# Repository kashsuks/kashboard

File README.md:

# kashboard

**kasboard** is a devboard that is (sorta) based off me. It is a rp2040 based devboard that follows [this](https://blueprint.hackclub.com/guides/devboard). I added a neopixel _APA102_ that will act as a status light to indicate when the board is turned on and when it is not.

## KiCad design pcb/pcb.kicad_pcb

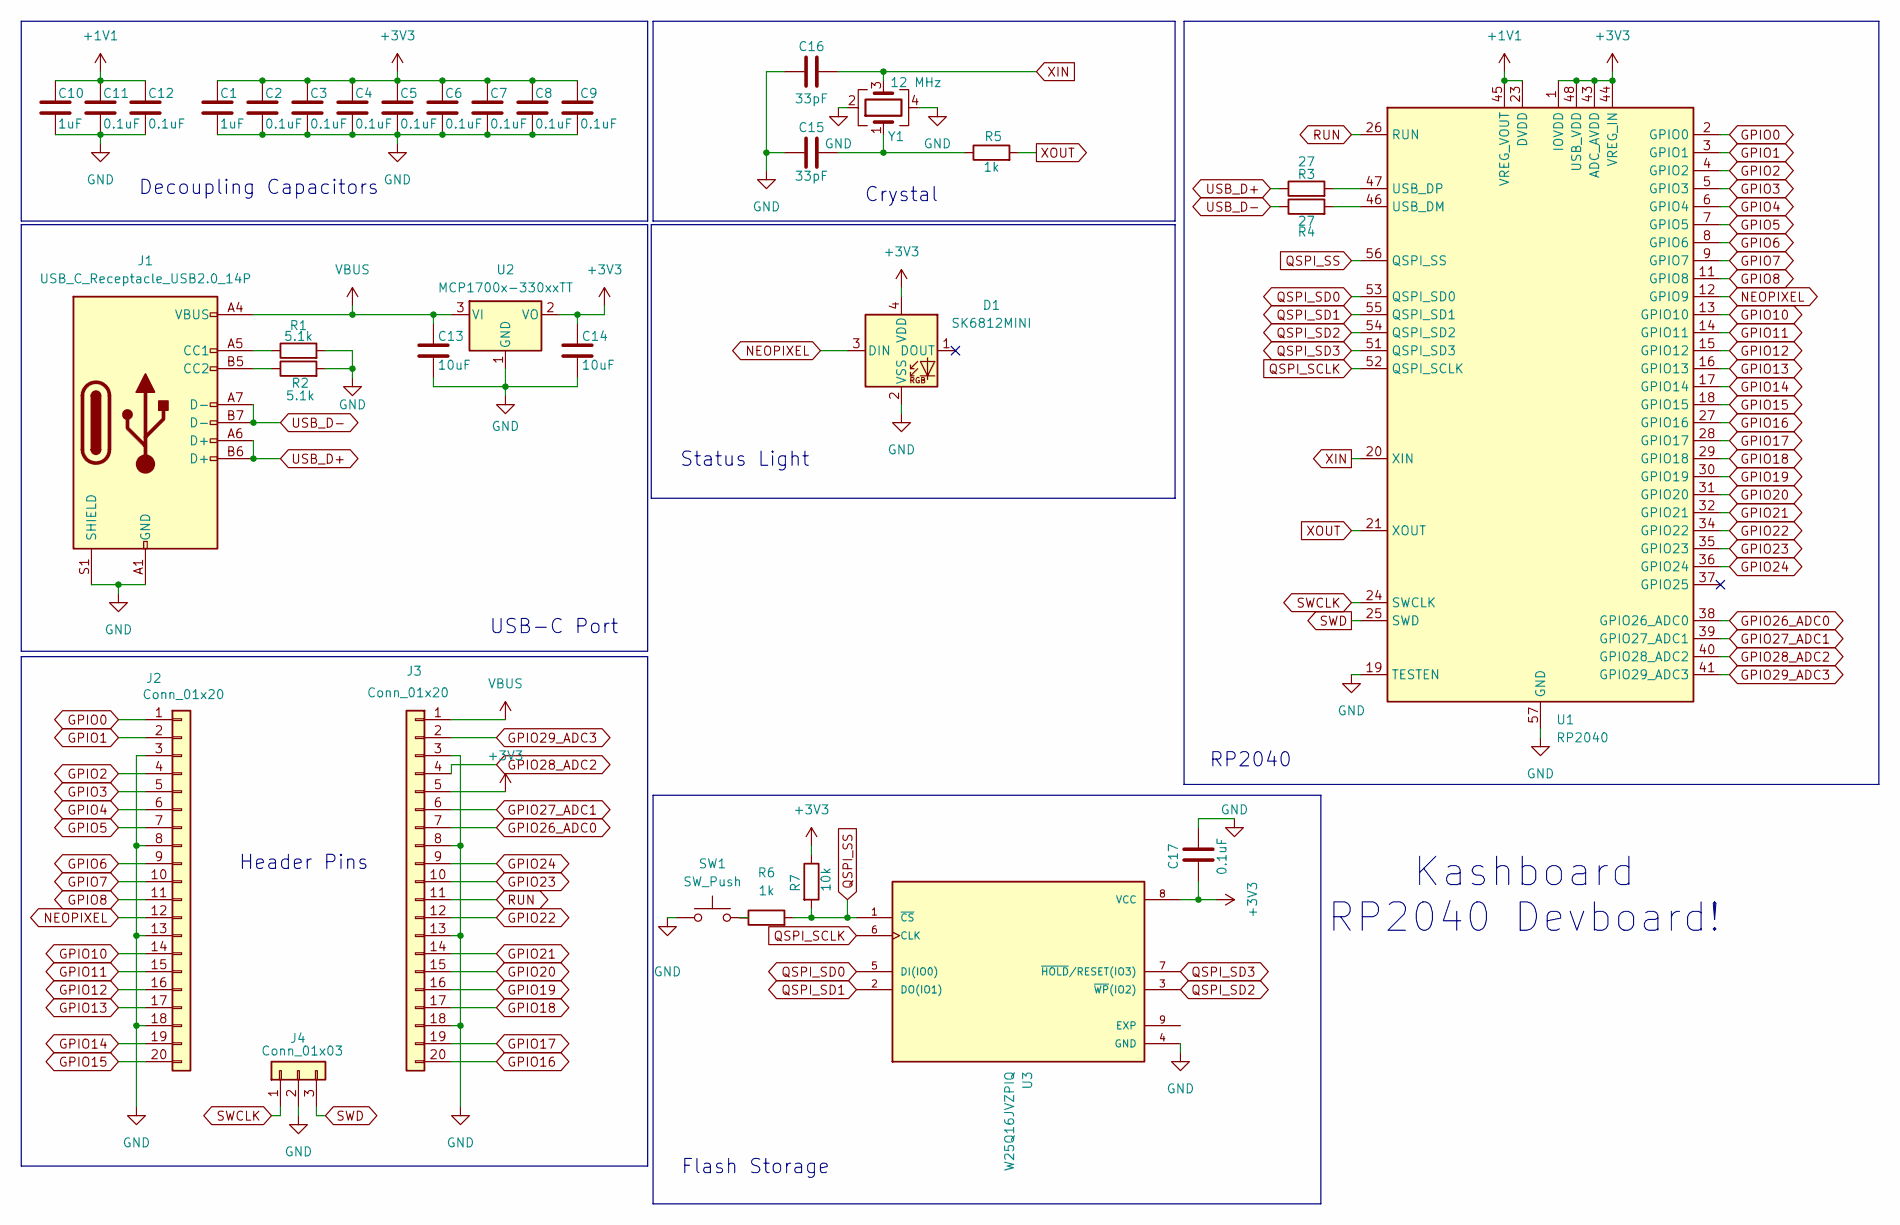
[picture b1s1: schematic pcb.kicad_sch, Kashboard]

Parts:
C1, C10: 1uF; C_0402_1005Metric
C2, C3, C4, C5, C6, C7, C8, C9, C11, C12, C17: 0.1uF; C_0402_1005Metric
C13, C14: 10uF; C_0402_1005Metric
C15, C16: 33pF; C_0402_1005Metric
D1: SK6812MINI; LED_SK6812MINI_PLCC4_3.5x3.5mm_P1.75mm
J1: USB_C_Receptacle_USB2.0_14P; USB_C_Receptacle_HRO_TYPE-C-31-M-12
J2, J3: Conn_01x20; PinHeader_1x20_P2.54mm_Vertical
J4: Conn_01x03; PinHeader_1x03_P2.54mm_Vertical
R1, R2: 5.1k; R_0402_1005Metric
R3, R4: 27; R_0402_1005Metric
R5, R6: 1k; R_0402_1005Metric
R7: 10k; R_0402_1005Metric
SW1: SW_Push; SW_Push_SPST_NO_Alps_SKRK
U1: RP2040; QFN-56-1EP_7x7mm_P0.4mm_EP3.2x3.2mm
U2: MCP1700x-330xxTT; SOT-23
U3: W25Q16JVZPIQ; Winbond_USON-8-1EP_3x2mm_P0.5mm_EP0.2x1.6mm
Y1: 12 MHz; Crystal_SMD_3225-4Pin_3.2x2.5mm

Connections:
+1V1: C10.1, C11.1, C12.1, U1.23 (DVDD), U1.45 (VREG_VOUT), U1.50 (DVDD)
+3V3: C1.1, C2.1, C3.1, C4.1, C5.1, C6.1, C7.1, C8.1, C9.1, C14.2, C17.2, D1.4 (VDD), J3.5, R7.1, U1.1 (IOVDD), U1.10 (IOVDD), U1.22 (IOVDD), U1.33 (IOVDD), U1.42 (IOVDD), U1.43 (ADC_AVDD), U1.44 (VREG_IN), U1.48 (USB_VDD), U1.49 (IOVDD), U2.2 (VO), U3.8 (VCC); also elsewhere on the board
GND: C1.2, C2.2, C3.2, C4.2, C5.2, C6.2, C7.2, C8.2, C9.2, C10.2, C11.2, C12.2, C13.1, C14.1, C15.1, C16.1, C17.1, D1.2 (VSS), J1.A1 (GND), J1.A12 (GND), J1.B1 (GND), J1.B12 (GND), J1.S1 (SHIELD), J2.3, J2.8, J2.13, J2.18, J3.3, J3.8, J3.13, J3.18, J4.2, R1.2, R2.2, SW1.1, U1.19 (TESTEN), U1.57 (GND), U2.1 (GND), U3.4 (GND), Y1.2, Y1.4; also elsewhere on the board
GPIO0: J2.1, U1.2 (GPIO0)
GPIO1: J2.2, U1.3 (GPIO1)
GPIO2: J2.4, U1.4 (GPIO2)
GPIO3: J2.5, U1.5 (GPIO3)
GPIO4: J2.6, U1.6 (GPIO4)
GPIO5: J2.7, U1.7 (GPIO5)
GPIO6: J2.9, U1.8 (GPIO6)
GPIO7: J2.10, U1.9 (GPIO7)
GPIO8: J2.11, U1.11 (GPIO8)
GPIO10: J2.14, U1.13 (GPIO10)
GPIO11: J2.15, U1.14 (GPIO11)
GPIO12: J2.16, U1.15 (GPIO12)
GPIO13: J2.17, U1.16 (GPIO13)
GPIO14: J2.19, U1.17 (GPIO14)
GPIO15: J2.20, U1.18 (GPIO15)
GPIO16: J3.20, U1.27 (GPIO16)
GPIO17: J3.19, U1.28 (GPIO17)
GPIO18: J3.17, U1.29 (GPIO18)
GPIO19: J3.16, U1.30 (GPIO19)
GPIO20: J3.15, U1.31 (GPIO20)
GPIO21: J3.14, U1.32 (GPIO21)
GPIO22: J3.12, U1.34 (GPIO22)
GPIO23: J3.10, U1.35 (GPIO23)
GPIO24: J3.9, U1.36 (GPIO24)
GPIO26_ADC0: J3.7, U1.38 (GPIO26_ADC0)
GPIO27_ADC1: J3.6, U1.39 (GPIO27_ADC1)
GPIO28_ADC2: J3.4, U1.40 (GPIO28_ADC2)
GPIO29_ADC3: J3.2, U1.41 (GPIO29_ADC3)
NEOPIXEL: D1.3 (DIN), J2.12, U1.12 (GPIO9)
unnamed: C15.2, R5.1, Y1.1
unnamed: J1.A5 (CC1), R1.1
unnamed: J1.B5 (CC2), R2.1
unnamed: R6.1, SW1.2
unnamed: R4.2, U1.46 (USB_DM)
unnamed: R3.2, U1.47 (USB_DP)
QSPI_SCLK: U1.52 (QSPI_SCLK), U3.6 (CLK)
QSPI_SD0: U1.53 (QSPI_SD0), U3.5 (DI(IO0))
QSPI_SD1: U1.55 (QSPI_SD1), U3.2 (DO(IO1))
QSPI_SD2: U1.54 (QSPI_SD2), U3.3 (~WP(IO2))
QSPI_SD3: U1.51 (QSPI_SD3), U3.7 (~HOLD/RESET(IO3))
QSPI_SS: R6.2, R7.2, U1.56 (QSPI_SS), U3.1 (~CS)
RUN: J3.11, U1.26 (RUN)
SWCLK: J4.1, U1.24 (SWCLK)
SWD: J4.3, U1.25 (SWD)
USB_D+: J1.A6 (D+), J1.B6 (D+), R3.1
USB_D-: J1.A7 (D-), J1.B7 (D-), R4.1
VBUS: C13.2, J1.A4 (VBUS), J1.A9 (VBUS), J1.B4 (VBUS), J1.B9 (VBUS), J3.1, U2.3 (VI)
XIN: C16.2, U1.20 (XIN), Y1.3
XOUT: R5.2, U1.21 (XOUT)

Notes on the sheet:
Header Pins
Flash Storage
Crystal
Decoupling Capacitors
RP2040
USB-C Port
Status Light
Kashboard RP2040 Devboard!

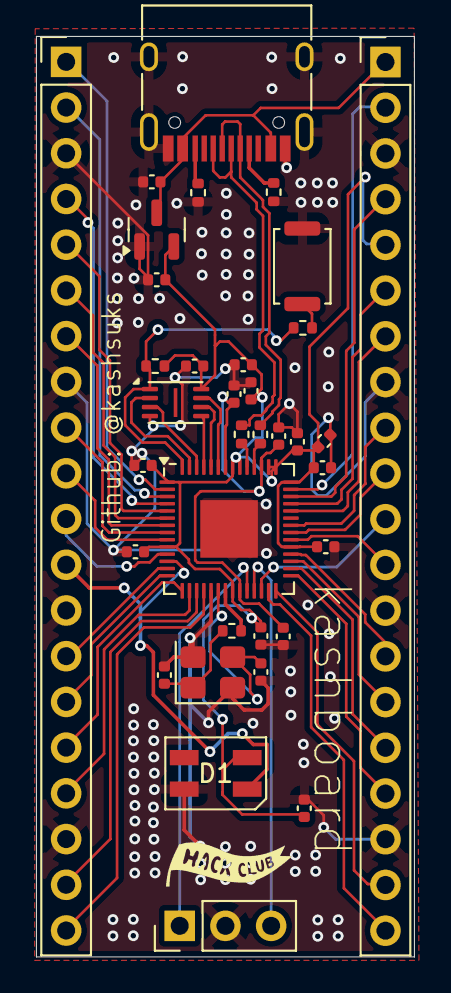
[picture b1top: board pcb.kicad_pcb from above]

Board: 2 copper layers, 21.0 x 51.1 mm, 35 parts (0 on the bottom side), 52 nets.

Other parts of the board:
C18: 0.1uF; C_0402_1005Metric

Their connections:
+3V3: C18.1; also elsewhere on the board
GND: C18.2; also elsewhere on the board

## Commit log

2025-10-04 got upto the usb-c part
2025-10-04 logging off for the night - completed the schematic
2025-10-04 feat: added the neopixel status led
2025-10-04 finished the schematic and added it to the pcb
2025-10-04 updated the schematic with better formatting
2025-10-05 feat: updated most of the pcb, still have some capacitors to wire
2025-10-05 last save for today
2025-10-05 holy shit massive update the pcb routing is done
2025-10-06 better routing completed
2025-10-06 added some more vias and lined them up
2025-10-06 added silkscreen
2025-10-06 Added production files
2025-10-06 removed the debugging drc report
2025-10-06 [fix] Updated gitignore to remove DS_STORE
2025-10-06 Revise README to enhance project overview
    Updated project description for clarity.
2025-10-08 replaced the apa102 with sk6182 neopixel
2025-10-08 added the sk6182 mini 3d model to 3d render
2025-10-08 added schem, pcb, top, and bot renders
2025-10-08 added new production files
2025-10-13 daily update of pcb files
2025-10-13 added code
